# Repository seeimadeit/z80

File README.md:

# z80
my z80 based computer

my tools
---- arduino mega ----
during project startup im using it to provide a clock source and a serial port configured as a device on the z80 so I use it for basic keyboard IO.
the project will remove this at some point in the future..
https://www.arduino.cc/en/software

----- chip programmer ---
tl866II plus
www.xgecu.com
rom - at28c64b
gal - ATF16LV8CZ - provides logic for rom and ram selection.
source code for GAL and ROM available on github

------ svn tool ---
oxygenxml

----- gal programming language ----
wincupl

https://www.microchip.com/design-centers/fpgas-and-plds/splds-cplds/pld-design-resources

-------- rom code -----
vasm
http://sun.hasenbraten.de/vasm/
initial rom code written with vasm. I'll be moving to z88dk in the future.

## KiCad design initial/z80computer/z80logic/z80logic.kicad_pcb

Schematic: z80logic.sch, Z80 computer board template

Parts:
ANDWAIT1: SN74HC21N; DIP-14_W7.62mm_Socket
C1, C9: 0.1uF; C_Axial_L5.1mm_D3.1mm_P7.50mm_Horizontal
C2, C4, C12, C13: perf_9x4symbol; perf_9x4
C3: 1.0uF; C_Axial_L3.8mm_D2.6mm_P7.50mm_Horizontal
C5, C14, C15, C16, C17, C18, C19, C20: perf_13x4symbol; perf_13x4
C6, C10, C11: perf_12x4symbol; perf_12x4
C7, C8: perf_36x4symbol; perf_36x4
CLOCK1: PIC18F24Q10-xSP; DIP-28_W7.62mm
IOPORT1: GAL16V8; DIP-20_W7.62mm_Socket
J1: pin header 855-M20-9953645; PinHeader_2x36_P2.54mm_Horizontal
J2: Conn_02x03_Top_Bottom; PinHeader_2x03_P2.54mm_Horizontal
J3: Conn_02x03_Odd_Even; PinSocket_2x03_P2.54mm_Vertical
MEMCHIPSELECT1: MEMCHIPSELECT; DIP-20_W7.62mm_Socket
OR1: SN74LS32N; DIP-14_W7.62mm_Socket
R1, R2: 1K; R_Axial_DIN0207_L6.3mm_D2.5mm_P10.16mm_Horizontal
SW1: SW_SPST; SW_PUSH_6mm_H8mm

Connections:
/17: C7.33, C7.34, C7.35, C7.36, J1.17
/18: C8.33, C8.34, C8.35, C8.36, J1.18
/27: C7.53, C7.54, C7.55, C7.56, J1.27
/28: C8.53, C8.54, C8.55, C8.56, J1.28
/42: C8.81, C8.82, C8.83, C8.84, J1.42
/43: C7.85, C7.86, C7.87, C7.88, J1.43
/44: C8.85, C8.86, C8.87, C8.88, J1.44
/48: C8.93, C8.94, C8.95, C8.96, J1.48
/49: C7.97, C7.98, C7.99, C7.100, J1.49
/50: C8.97, C8.98, C8.99, C8.100, J1.50
/54: C8.105, C8.106, C8.107, C8.108, J1.54
/55: C7.109, C7.110, C7.111, C7.112, J1.55
/56: C8.109, C8.110, C8.111, C8.112, J1.56
/60: C8.117, C8.118, C8.119, C8.120, J1.60
/61: C7.121, C7.122, C7.123, C7.124, J1.61
/62: C8.121, C8.122, C8.123, C8.124, J1.62
/63: C7.125, C7.126, C7.127, C7.128, J1.63
/64: C8.125, C8.126, C8.127, C8.128, J1.64
/65: C7.129, C7.130, C7.131, C7.132, J1.65
/66: C8.129, C8.130, C8.131, C8.132, J1.66
/67: C7.133, C7.134, C7.135, C7.136, J1.67
/68: C8.133, C8.134, C8.135, C8.136, J1.68
/69: C7.137, C7.138, C7.139, C7.140, J1.69
/70: C8.137, C8.138, C8.139, C8.140, J1.70
/71: C7.141, C7.142, C7.143, C7.144, J1.71
/72: C8.141, C8.142, C8.143, C8.144, J1.72
/A0: C7.1, C7.2, C7.3, C7.4, C12.1, C12.2, C12.3, C12.4, IOPORT1.1, J1.1
/A1: C8.1, C8.2, C8.3, C8.4, C12.5, C12.6, C12.7, C12.8, IOPORT1.2, J1.2
/A1A: ANDWAIT1.1, C10.1, C10.2, C10.3, C10.4
/A1B: ANDWAIT1.2, C10.5, C10.6, C10.7, C10.8
/A1C: ANDWAIT1.4, C10.9, C10.10, C10.11, C10.12
/A1CS: C4.25, C4.26, C4.27, C4.28, C7.105, C7.106, C7.107, C7.108, J1.53, MEMCHIPSELECT1.13
/A1D: ANDWAIT1.5, C10.13, C10.14, C10.15, C10.16
/A1OE: C8.101, C8.102, C8.103, C8.104, J1.52
/A1WE: C7.101, C7.102, C7.103, C7.104, J1.51
/A1Y: ANDWAIT1.6, C10.17, C10.18, C10.19, C10.20
/A2: C7.5, C7.6, C7.7, C7.8, C12.9, C12.10, C12.11, C12.12, IOPORT1.3, J1.3
/A2A: ANDWAIT1.9, C10.21, C10.22, C10.23, C10.24
/A2B: ANDWAIT1.10, C10.25, C10.26, C10.27, C10.28
/A2C: ANDWAIT1.12, C10.29, C10.30, C10.31, C10.32
/A2CS: C4.21, C4.22, C4.23, C4.24, C7.117, C7.118, C7.119, C7.120, J1.59, MEMCHIPSELECT1.14
/A2D: ANDWAIT1.13, C10.33, C10.34, C10.35, C10.36
/A2OE: C8.113, C8.114, C8.115, C8.116, J1.58
/A2WE: C7.113, C7.114, C7.115, C7.116, J1.57
/A2Y: ANDWAIT1.8, C10.37, C10.38, C10.39, C10.40
/A3: C8.5, C8.6, C8.7, C8.8, C12.13, C12.14, C12.15, C12.16, IOPORT1.4, J1.4
/A4: C7.9, C7.10, C7.11, C7.12, J1.5
/A5: C8.9, C8.10, C8.11, C8.12, J1.6
/A6: C7.13, C7.14, C7.15, C7.16, J1.7
/A7: C8.13, C8.14, C8.15, C8.16, J1.8
/A8: C7.17, C7.18, C7.19, C7.20, J1.9
/A9: C8.17, C8.18, C8.19, C8.20, J1.10
/A10: C7.21, C7.22, C7.23, C7.24, J1.11
/A11: C2.17, C2.18, C2.19, C2.20, C8.21, C8.22, C8.23, C8.24, J1.12, MEMCHIPSELECT1.5
/A12: C2.21, C2.22, C2.23, C2.24, C7.25, C7.26, C7.27, C7.28, J1.13, MEMCHIPSELECT1.6
/A13: C2.25, C2.26, C2.27, C2.28, C8.25, C8.26, C8.27, C8.28, J1.14, MEMCHIPSELECT1.7
/A14: C2.29, C2.30, C2.31, C2.32, C7.29, C7.30, C7.31, C7.32, J1.15, MEMCHIPSELECT1.8
/A15: C2.33, C2.34, C2.35, C2.36, C8.29, C8.30, C8.31, C8.32, J1.16, MEMCHIPSELECT1.9
/BUSACK: C7.57, C7.58, C7.59, C7.60, J1.29
/BUSRQ: C8.57, C8.58, C8.59, C8.60, J1.30
/CLK: C5.33, C5.34, C5.35, C5.36, C7.81, C7.82, C7.83, C7.84, CLOCK1.10, J1.41
/D0: C7.37, C7.38, C7.39, C7.40, J1.19
/D1: C8.37, C8.38, C8.39, C8.40, J1.20
/D2: C7.41, C7.42, C7.43, C7.44, J1.21
/D3: C8.41, C8.42, C8.43, C8.44, J1.22
/D4: C7.45, C7.46, C7.47, C7.48, J1.23
/D5: C8.45, C8.46, C8.47, C8.48, J1.24
/D6: C7.49, C7.50, C7.51, C7.52, J1.25
/D7: C8.49, C8.50, C8.51, C8.52, J1.26
/GND: ANDWAIT1.7, C1.2, C3.2, C9.2, CLOCK1.19, IOPORT1.10, J2.6, J3.5, MEMCHIPSELECT1.10, OR1.7, SW1.2
/HALT: C7.69, C7.70, C7.71, C7.72, J1.35
/INT: C7.77, C7.78, C7.79, C7.80, J1.39
/IORQ: C4.9, C4.10, C4.11, C4.12, C7.61, C7.62, C7.63, C7.64, C12.17, C12.18, C12.19, C12.20, IOPORT1.5, J1.31, MEMCHIPSELECT1.17
/M1: C8.73, C8.74, C8.75, C8.76, C12.29, C12.30, C12.31, C12.32, IOPORT1.8, J1.38
/MREQ: C4.33, C4.34, C4.35, C4.36, C8.61, C8.62, C8.63, C8.64, J1.32, MEMCHIPSELECT1.11
/NMI: C8.77, C8.78, C8.79, C8.80, J1.40
/O1A: C11.1, C11.2, C11.3, C11.4, OR1.1
/O1B: C11.5, C11.6, C11.7, C11.8, OR1.2
/O1Y: C11.9, C11.10, C11.11, C11.12, OR1.3
/O2A: C11.13, C11.14, C11.15, C11.16, OR1.4
/O2B: C11.17, C11.18, C11.19, C11.20, OR1.5
/O2Y: C11.21, C11.22, C11.23, C11.24, OR1.6
/O3A: C11.25, C11.26, C11.27, C11.28, OR1.9
/O3B: C11.29, C11.30, C11.31, C11.32, OR1.10
/O3Y: C11.33, C11.34, C11.35, C11.36, OR1.8
/O4A: C11.37, C11.38, C11.39, C11.40, OR1.12
/O4B: C11.41, C11.42, C11.43, C11.44, OR1.13
/O4Y: C11.45, C11.46, C11.47, C11.48, OR1.11
/OCS: C4.29, C4.30, C4.31, C4.32, C7.93, C7.94, C7.95, C7.96, J1.47, MEMCHIPSELECT1.12
/OOE: C8.89, C8.90, C8.91, C8.92, J1.46
/OWE: C7.89, C7.90, C7.91, C7.92, J1.45
/POWER2: J2.2, J3.1
/POWER3: J2.3, J3.4
/PUSH: C6.41, C6.42, C6.43, C6.44, CLOCK1.16, R2.2
/RD: C8.65, C8.66, C8.67, C8.68, J1.34
/RESET: J2.1, J3.2
/RFSH: C4.17, C4.18, C4.19, C4.20, C7.73, C7.74, C7.75, C7.76, C12.21, C12.22, C12.23, C12.24, IOPORT1.6, J1.37, MEMCHIPSELECT1.15
/VCC3: J2.4, J3.3
/VCC5: ANDWAIT1.14, C1.1, C3.1, C5.1, C5.2, C5.3, C5.4, C9.1, C14.4, C14.8, C14.12, C14.16, C14.20, C14.24, C14.28, C14.32, C14.36, C14.40, C14.44, C14.48, C14.52, C17.49, C17.50, C17.51, C17.52, CLOCK1.1, CLOCK1.8, CLOCK1.20, IOPORT1.20, J2.5, J3.6, MEMCHIPSELECT1.20, OR1.14, R1.2
/WAIT: C8.69, C8.70, C8.71, C8.72, J1.36
/WR: C7.65, C7.66, C7.67, C7.68, J1.33
unnamed: C2.1, C2.2, C2.3, C2.4, MEMCHIPSELECT1.1
unnamed: C2.5, C2.6, C2.7, C2.8, MEMCHIPSELECT1.2
unnamed: C2.9, C2.10, C2.11, C2.12, MEMCHIPSELECT1.3
unnamed: C2.13, C2.14, C2.15, C2.16, MEMCHIPSELECT1.4
unnamed: C4.1, C4.2, C4.3, C4.4, MEMCHIPSELECT1.19
unnamed: C4.5, C4.6, C4.7, C4.8, MEMCHIPSELECT1.18
unnamed: C4.13, C4.14, C4.15, C4.16, MEMCHIPSELECT1.16
unnamed: C5.5, C5.6, C5.7, C5.8, CLOCK1.2
unnamed: C5.9, C5.10, C5.11, C5.12, CLOCK1.3
unnamed: C5.13, C5.14, C5.15, C5.16, CLOCK1.4
unnamed: C5.17, C5.18, C5.19, C5.20, CLOCK1.5
unnamed: C5.21, C5.22, C5.23, C5.24, CLOCK1.6
unnamed: C5.25, C5.26, C5.27, C5.28, CLOCK1.7
unnamed: C5.29, C5.30, C5.31, C5.32, CLOCK1.9
unnamed: C5.37, C5.38, C5.39, C5.40, CLOCK1.11
unnamed: C5.41, C5.42, C5.43, C5.44, CLOCK1.12
unnamed: C5.45, C5.46, C5.47, C5.48, CLOCK1.13
unnamed: C5.49, C5.50, C5.51, C5.52, CLOCK1.14
unnamed: C6.1, C6.2, C6.3, C6.4, CLOCK1.28
unnamed: C6.5, C6.6, C6.7, C6.8, CLOCK1.27
unnamed: C6.9, C6.10, C6.11, C6.12, CLOCK1.26
unnamed: C6.13, C6.14, C6.15, C6.16, CLOCK1.25
unnamed: C6.17, C6.18, C6.19, C6.20, CLOCK1.24
unnamed: C6.21, C6.22, C6.23, C6.24, CLOCK1.23
unnamed: C6.25, C6.26, C6.27, C6.28, CLOCK1.22
unnamed: C6.29, C6.30, C6.31, C6.32, CLOCK1.21
unnamed: C6.33, C6.34, C6.35, C6.36, CLOCK1.18
unnamed: C6.37, C6.38, C6.39, C6.40, CLOCK1.17
unnamed: C6.45, C6.46, C6.47, C6.48, CLOCK1.15
unnamed: C10.41, C10.42, C10.43, C10.44
unnamed: C10.45, C10.46, C10.47, C10.48
unnamed: C12.25, C12.26, C12.27, C12.28, IOPORT1.7
unnamed: C12.33, C12.34, C12.35, C12.36, IOPORT1.9
unnamed: C13.1, C13.2, C13.3, C13.4, IOPORT1.19
unnamed: C13.5, C13.6, C13.7, C13.8, IOPORT1.18
unnamed: C13.9, C13.10, C13.11, C13.12, IOPORT1.17
unnamed: C13.13, C13.14, C13.15, C13.16, IOPORT1.16
unnamed: C13.17, C13.18, C13.19, C13.20, IOPORT1.15
unnamed: C13.21, C13.22, C13.23, C13.24, IOPORT1.14
unnamed: C13.25, C13.26, C13.27, C13.28, IOPORT1.13
unnamed: C13.29, C13.30, C13.31, C13.32, IOPORT1.12
unnamed: C13.33, C13.34, C13.35, C13.36, IOPORT1.11
unnamed: R1.1, R2.1, SW1.1

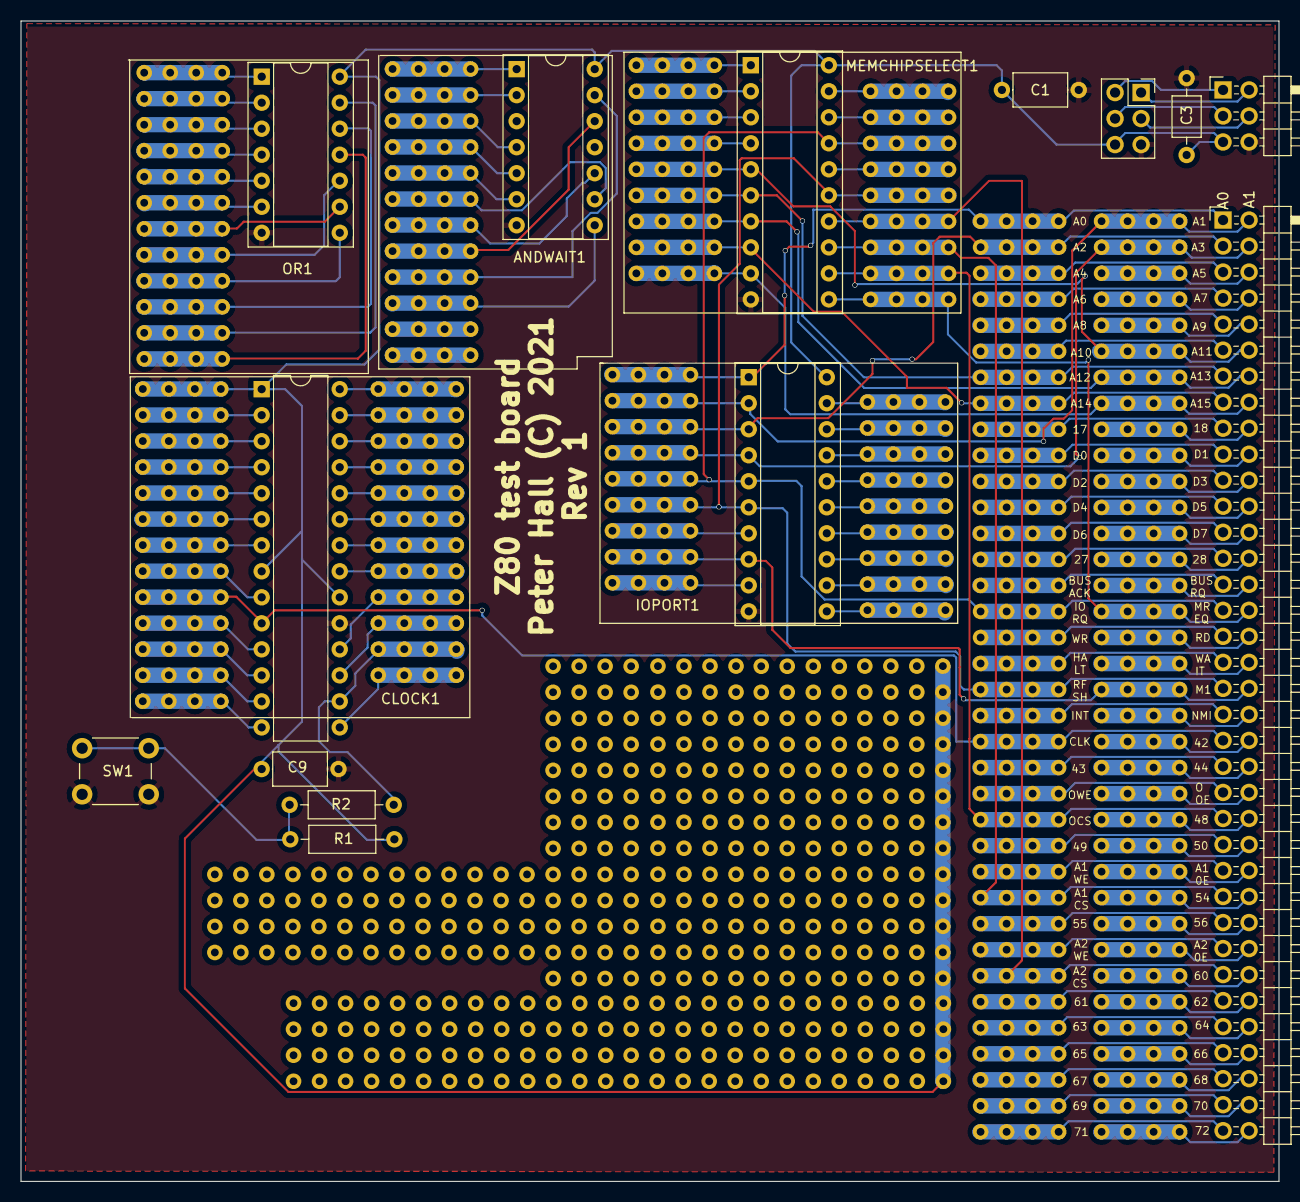
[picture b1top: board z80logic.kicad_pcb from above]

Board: 2 copper layers, 122.8 x 113.3 mm, 31 parts (0 on the bottom side), 144 nets.

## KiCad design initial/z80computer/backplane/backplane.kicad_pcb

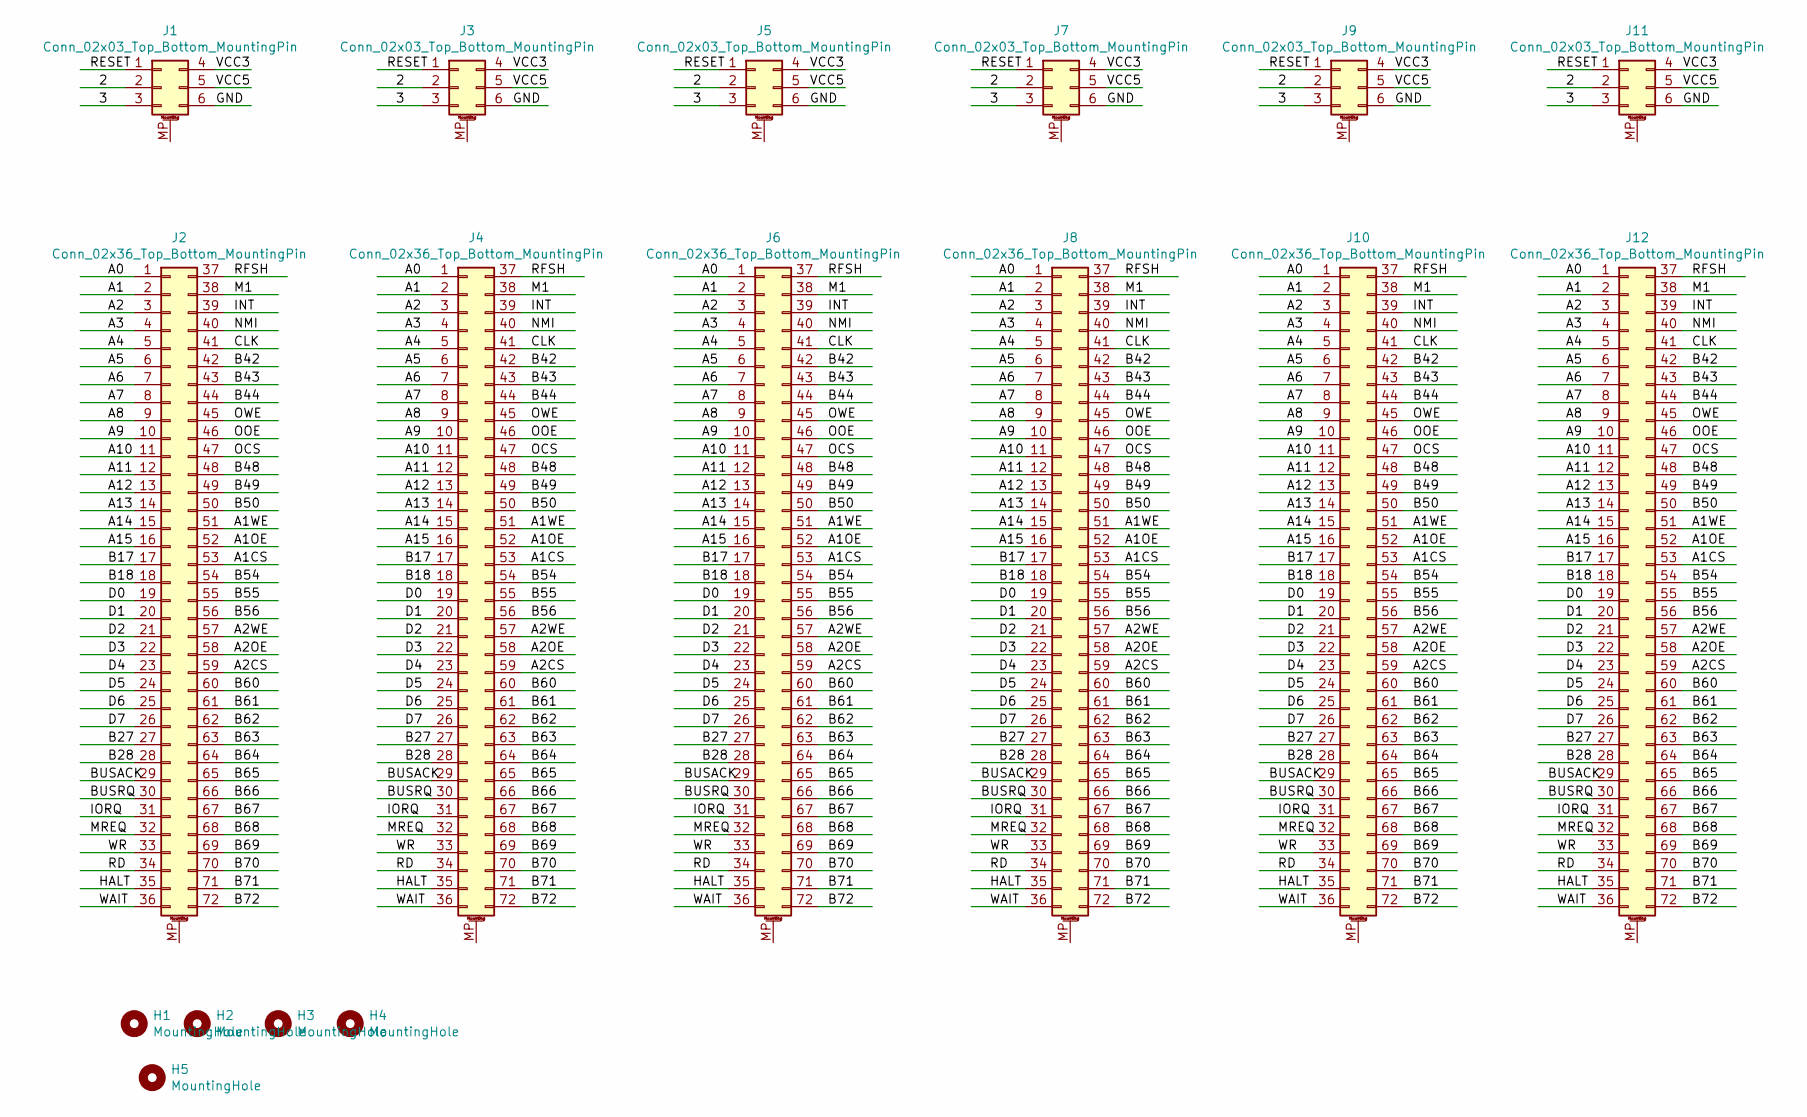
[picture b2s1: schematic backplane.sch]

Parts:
H1, H2, H3, H4: MountingHole; MountingHole_3mm_Pad_TopBottom
H5: MountingHole; MountingHole_2.1mm
J1, J3, J5, J7, J9, J11: Conn_02x03_Top_Bottom_MountingPin; PinSocket_2x03_P2.54mm_Vertical
J2, J4, J6, J8, J10, J12: Conn_02x36_Top_Bottom_MountingPin; PinSocket_2x36_P2.54mm_Vertical

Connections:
/2: J1.2, J3.2, J5.2, J7.2, J9.2, J11.2
/3: J1.3, J3.3, J5.3, J7.3, J9.3, J11.3
/A0: J2.1, J4.1, J6.1, J8.1, J10.1, J12.1
/A1: J2.2, J4.2, J6.2, J8.2, J10.2, J12.2
/A1CS: J2.53, J4.53, J6.53, J8.53, J10.53, J12.53
/A1OE: J2.52, J4.52, J6.52, J8.52, J10.52, J12.52
/A1WE: J2.51, J4.51, J6.51, J8.51, J10.51, J12.51
/A2: J2.3, J4.3, J6.3, J8.3, J10.3, J12.3
/A2CS: J2.59, J4.59, J6.59, J8.59, J10.59, J12.59
/A2OE: J2.58, J4.58, J6.58, J8.58, J10.58, J12.58
/A2WE: J2.57, J4.57, J6.57, J8.57, J10.57, J12.57
/A3: J2.4, J4.4, J6.4, J8.4, J10.4, J12.4
/A4: J2.5, J4.5, J6.5, J8.5, J10.5, J12.5
/A5: J2.6, J4.6, J6.6, J8.6, J10.6, J12.6
/A6: J2.7, J4.7, J6.7, J8.7, J10.7, J12.7
/A7: J2.8, J4.8, J6.8, J8.8, J10.8, J12.8
/A8: J2.9, J4.9, J6.9, J8.9, J10.9, J12.9
/A9: J2.10, J4.10, J6.10, J8.10, J10.10, J12.10
/A10: J2.11, J4.11, J6.11, J8.11, J10.11, J12.11
/A11: J2.12, J4.12, J6.12, J8.12, J10.12, J12.12
/A12: J2.13, J4.13, J6.13, J8.13, J10.13, J12.13
/A13: J2.14, J4.14, J6.14, J8.14, J10.14, J12.14
/A14: J2.15, J4.15, J6.15, J8.15, J10.15, J12.15
/A15: J2.16, J4.16, J6.16, J8.16, J10.16, J12.16
/B17: J2.17, J4.17, J6.17, J8.17, J10.17, J12.17
/B18: J2.18, J4.18, J6.18, J8.18, J10.18, J12.18
/B27: J2.27, J4.27, J6.27, J8.27, J10.27, J12.27
/B28: J2.28, J4.28, J6.28, J8.28, J10.28, J12.28
/B42: J2.42, J4.42, J6.42, J8.42, J10.42, J12.42
/B43: J2.43, J4.43, J6.43, J8.43, J10.43, J12.43
/B44: J2.44, J4.44, J6.44, J8.44, J10.44, J12.44
/B48: J2.48, J4.48, J6.48, J8.48, J10.48, J12.48
/B49: J2.49, J4.49, J6.49, J8.49, J10.49, J12.49
/B50: J2.50, J4.50, J6.50, J8.50, J10.50, J12.50
/B54: J2.54, J4.54, J6.54, J8.54, J10.54, J12.54
/B55: J2.55, J4.55, J6.55, J8.55, J10.55, J12.55
/B56: J2.56, J4.56, J6.56, J8.56, J10.56, J12.56
/B60: J2.60, J4.60, J6.60, J8.60, J10.60, J12.60
/B61: J2.61, J4.61, J6.61, J8.61, J10.61, J12.61
/B62: J2.62, J4.62, J6.62, J8.62, J10.62, J12.62
/B63: J2.63, J4.63, J6.63, J8.63, J10.63, J12.63
/B64: J2.64, J4.64, J6.64, J8.64, J10.64, J12.64
/B65: J2.65, J4.65, J6.65, J8.65, J10.65, J12.65
/B66: J2.66, J4.66, J6.66, J8.66, J10.66, J12.66
/B67: J2.67, J4.67, J6.67, J8.67, J10.67, J12.67
/B68: J2.68, J4.68, J6.68, J8.68, J10.68, J12.68
/B69: J2.69, J4.69, J6.69, J8.69, J10.69, J12.69
/B70: J2.70, J4.70, J6.70, J8.70, J10.70, J12.70
/B71: J2.71, J4.71, J6.71, J8.71, J10.71, J12.71
/B72: J2.72, J4.72, J6.72, J8.72, J10.72, J12.72
/BUSACK: J2.29, J4.29, J6.29, J8.29, J10.29, J12.29
/BUSRQ: J2.30, J4.30, J6.30, J8.30, J10.30, J12.30
/CLK: J2.41, J4.41, J6.41, J8.41, J10.41, J12.41
/D0: J2.19, J4.19, J6.19, J8.19, J10.19, J12.19
/D1: J2.20, J4.20, J6.20, J8.20, J10.20, J12.20
/D2: J2.21, J4.21, J6.21, J8.21, J10.21, J12.21
/D3: J2.22, J4.22, J6.22, J8.22, J10.22, J12.22
/D4: J2.23, J4.23, J6.23, J8.23, J10.23, J12.23
/D5: J2.24, J4.24, J6.24, J8.24, J10.24, J12.24
/D6: J2.25, J4.25, J6.25, J8.25, J10.25, J12.25
/D7: J2.26, J4.26, J6.26, J8.26, J10.26, J12.26
/GND: J1.6, J3.6, J5.6, J7.6, J9.6, J11.6
/HALT: J2.35, J4.35, J6.35, J8.35, J10.35, J12.35
/INT: J2.39, J4.39, J6.39, J8.39, J10.39, J12.39
/IORQ: J2.31, J4.31, J6.31, J8.31, J10.31, J12.31
/M1: J2.38, J4.38, J6.38, J8.38, J10.38, J12.38
/MREQ: J2.32, J4.32, J6.32, J8.32, J10.32, J12.32
/NMI: J2.40, J4.40, J6.40, J8.40, J10.40, J12.40
/OCS: J2.47, J4.47, J6.47, J8.47, J10.47, J12.47
/OOE: J2.46, J4.46, J6.46, J8.46, J10.46, J12.46
/OWE: J2.45, J4.45, J6.45, J8.45, J10.45, J12.45
/RD: J2.34, J4.34, J6.34, J8.34, J10.34, J12.34
/RESET: J1.1, J3.1, J5.1, J7.1, J9.1, J11.1
/RFSH: J2.37, J4.37, J6.37, J8.37, J10.37, J12.37
/VCC3: J1.4, J3.4, J5.4, J7.4, J9.4, J11.4
/VCC5: J1.5, J3.5, J5.5, J7.5, J9.5, J11.5
/WAIT: J2.36, J4.36, J6.36, J8.36, J10.36, J12.36
/WR: J2.33, J4.33, J6.33, J8.33, J10.33, J12.33

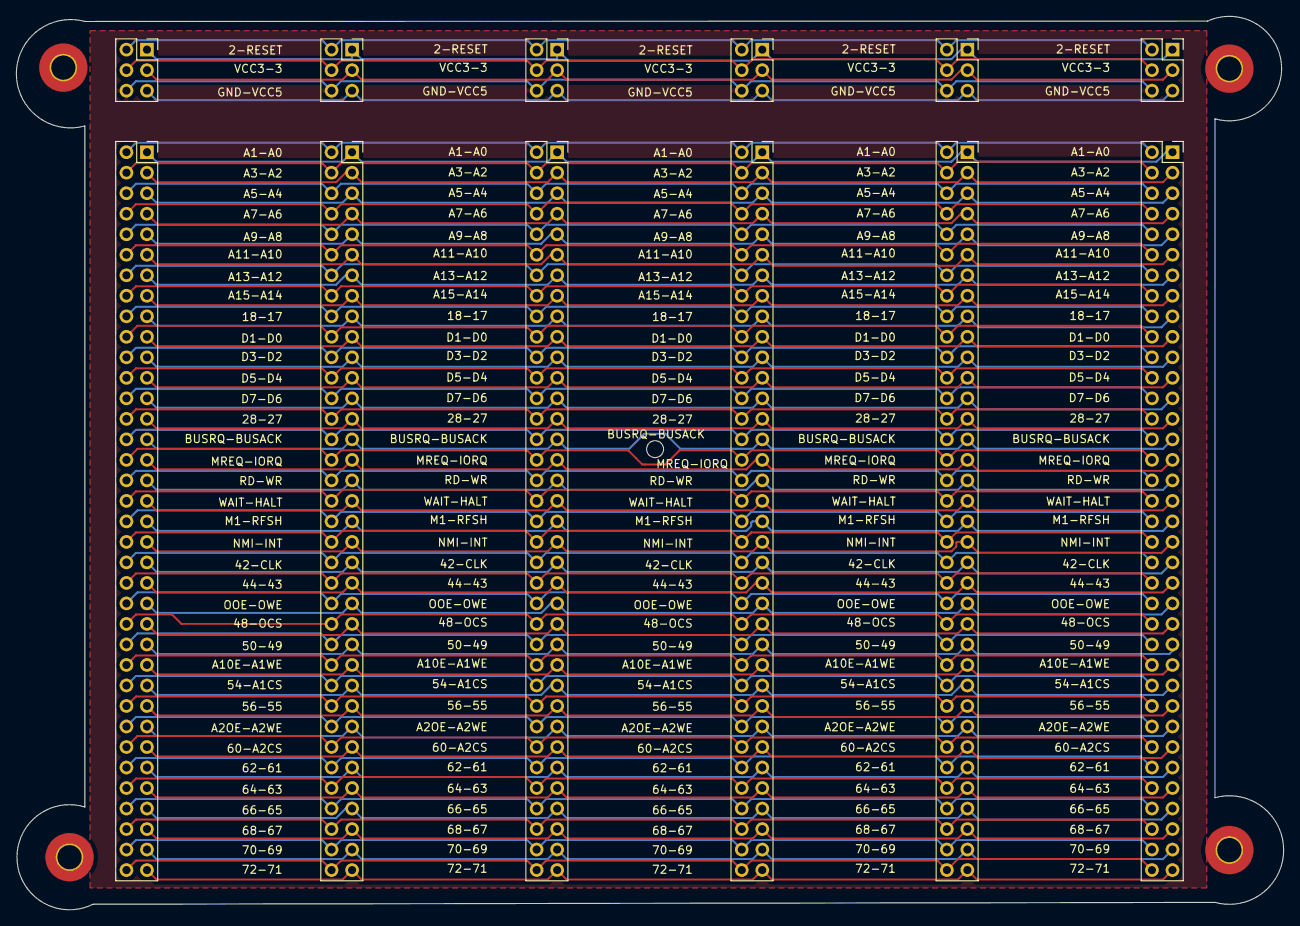
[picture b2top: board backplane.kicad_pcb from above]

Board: 2 copper layers, 156.9 x 110.6 mm, 17 parts (0 on the bottom side), 78 nets.

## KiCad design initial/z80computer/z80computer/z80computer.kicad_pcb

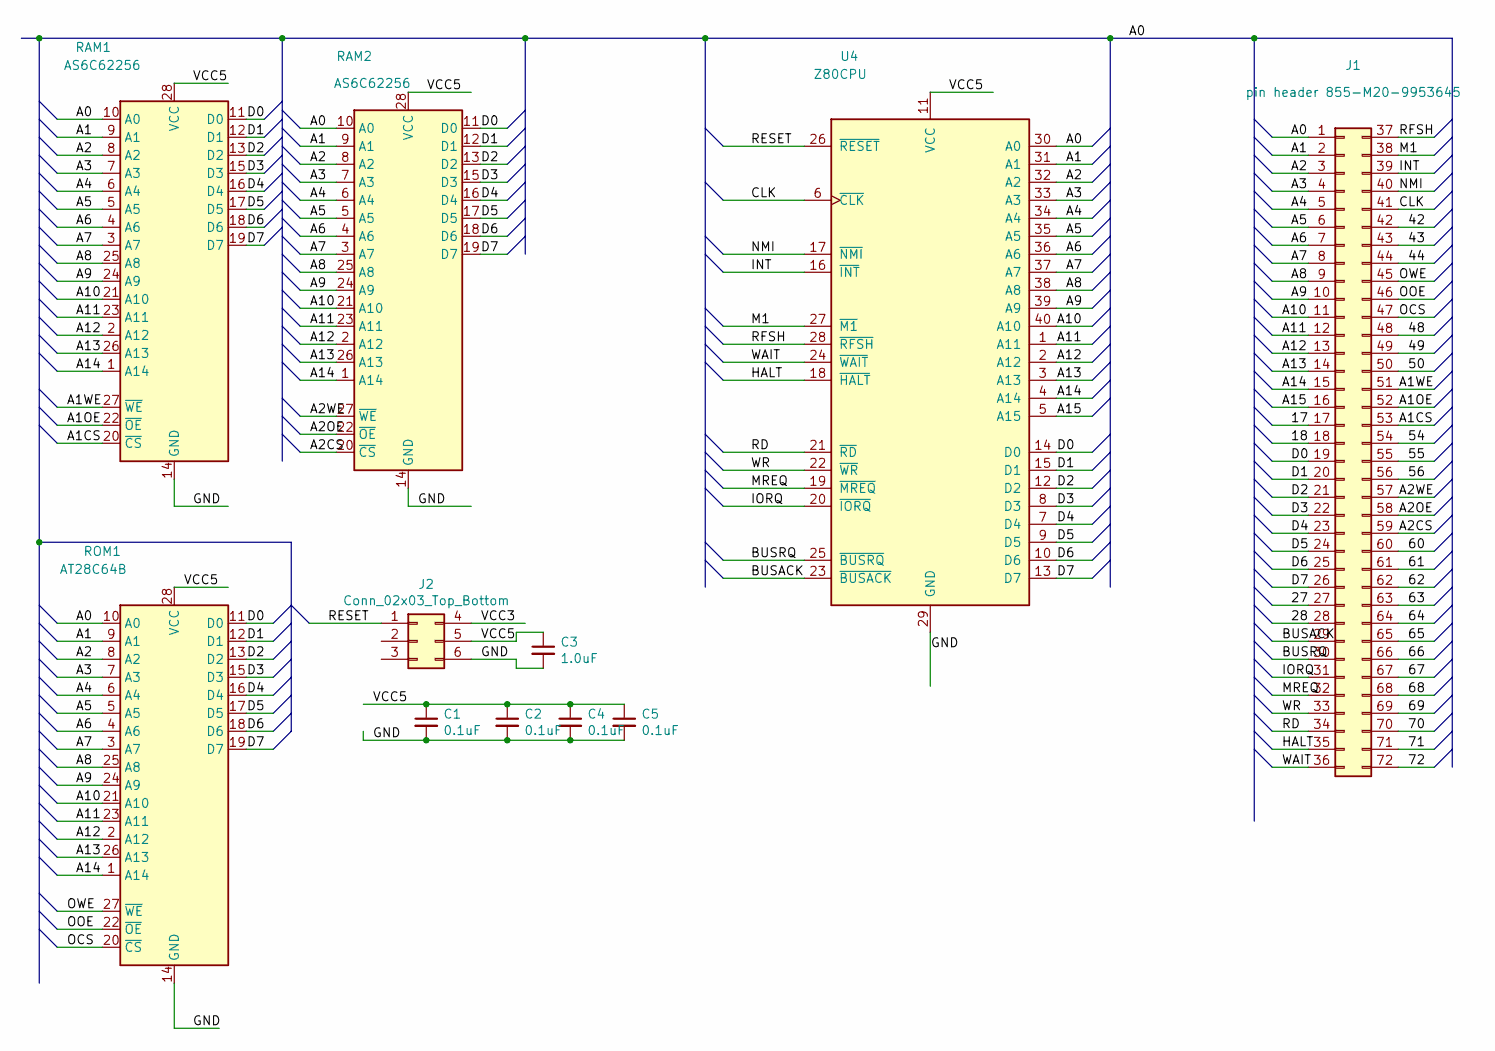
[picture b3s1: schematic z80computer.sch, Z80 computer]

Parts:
C1, C2, C4, C5: 0.1uF; C_Axial_L5.1mm_D3.1mm_P7.50mm_Horizontal
C3: 1.0uF; C_Axial_L3.8mm_D2.6mm_P7.50mm_Horizontal
J1: pin header 855-M20-9953645; PinHeader_2x36_P2.54mm_Horizontal
J2: Conn_02x03_Top_Bottom; PinHeader_2x03_P2.54mm_Horizontal
RAM1, RAM2: AS6C62256; DIP-28_W15.24mm_Socket_LongPads
ROM1: AT28C64B; DIP-28_W15.24mm_Socket_LongPads
U4: Z80CPU; DIP-40_W15.24mm_Socket_LongPads

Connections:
/A0: J1.1, RAM1.10 (A0), RAM2.10 (A0), ROM1.10 (A0), U4.30 (A0)
/A1: J1.2, RAM1.9 (A1), RAM2.9 (A1), ROM1.9 (A1), U4.31 (A1)
/A1CS: J1.53, RAM1.20 (~CS)
/A1OE: J1.52, RAM1.22 (~OE)
/A1WE: J1.51, RAM1.27 (~WE)
/A2: J1.3, RAM1.8 (A2), RAM2.8 (A2), ROM1.8 (A2), U4.32 (A2)
/A2CS: J1.59, RAM2.20 (~CS)
/A2OE: J1.58, RAM2.22 (~OE)
/A2WE: J1.57, RAM2.27 (~WE)
/A3: J1.4, RAM1.7 (A3), RAM2.7 (A3), ROM1.7 (A3), U4.33 (A3)
/A4: J1.5, RAM1.6 (A4), RAM2.6 (A4), ROM1.6 (A4), U4.34 (A4)
/A5: J1.6, RAM1.5 (A5), RAM2.5 (A5), ROM1.5 (A5), U4.35 (A5)
/A6: J1.7, RAM1.4 (A6), RAM2.4 (A6), ROM1.4 (A6), U4.36 (A6)
/A7: J1.8, RAM1.3 (A7), RAM2.3 (A7), ROM1.3 (A7), U4.37 (A7)
/A8: J1.9, RAM1.25 (A8), RAM2.25 (A8), ROM1.25 (A8), U4.38 (A8)
/A9: J1.10, RAM1.24 (A9), RAM2.24 (A9), ROM1.24 (A9), U4.39 (A9)
/A10: J1.11, RAM1.21 (A10), RAM2.21 (A10), ROM1.21 (A10), U4.40 (A10)
/A11: J1.12, RAM1.23 (A11), RAM2.23 (A11), ROM1.23 (A11), U4.1 (A11)
/A12: J1.13, RAM1.2 (A12), RAM2.2 (A12), ROM1.2 (A12), U4.2 (A12)
/A13: J1.14, RAM1.26 (A13), RAM2.26 (A13), ROM1.26 (A13), U4.3 (A13)
/A14: J1.15, RAM1.1 (A14), RAM2.1 (A14), ROM1.1 (A14), U4.4 (A14)
/A15: J1.16, U4.5 (A15)
/BUSACK: J1.29, U4.23 (~BUSACK~)
/BUSRQ: J1.30, U4.25 (~BUSRQ~)
/CLK: J1.41, U4.6 (~CLK~)
/D0: J1.19, RAM1.11 (D0), RAM2.11 (D0), ROM1.11 (D0), U4.14 (D0)
/D1: J1.20, RAM1.12 (D1), RAM2.12 (D1), ROM1.12 (D1), U4.15 (D1)
/D2: J1.21, RAM1.13 (D2), RAM2.13 (D2), ROM1.13 (D2), U4.12 (D2)
/D3: J1.22, RAM1.15 (D3), RAM2.15 (D3), ROM1.15 (D3), U4.8 (D3)
/D4: J1.23, RAM1.16 (D4), RAM2.16 (D4), ROM1.16 (D4), U4.7 (D4)
/D5: J1.24, RAM1.17 (D5), RAM2.17 (D5), ROM1.17 (D5), U4.9 (D5)
/D6: J1.25, RAM1.18 (D6), RAM2.18 (D6), ROM1.18 (D6), U4.10 (D6)
/D7: J1.26, RAM1.19 (D7), RAM2.19 (D7), ROM1.19 (D7), U4.13 (D7)
/GND: C1.2, C2.2, C3.2, C4.2, C5.2, J2.6, RAM1.14 (GND), RAM2.14 (GND), ROM1.14 (GND), U4.29 (GND)
/HALT: J1.35, U4.18 (~HALT~)
/INT: J1.39, U4.16 (~INT~)
/IORQ: J1.31, U4.20 (~IORQ~)
/M1: J1.38, U4.27 (~M1~)
/MREQ: J1.32, U4.19 (~MREQ~)
/NMI: J1.40, U4.17 (~NMI~)
/OCS: J1.47, ROM1.20 (~CS)
/OOE: J1.46, ROM1.22 (~OE)
/OWE: J1.45, ROM1.27 (~WE)
/RD: J1.34, U4.21 (~RD~)
/RESET: J2.1, U4.26 (~RESET~)
/RFSH: J1.37, U4.28 (~RFSH~)
/VCC3: J2.4
/VCC5: C1.1, C2.1, C3.1, C4.1, C5.1, J2.5, RAM1.28 (VCC), RAM2.28 (VCC), ROM1.28 (VCC), U4.11 (VCC)
/WAIT: J1.36, U4.24 (~WAIT~)
/WR: J1.33, U4.22 (~WR~)

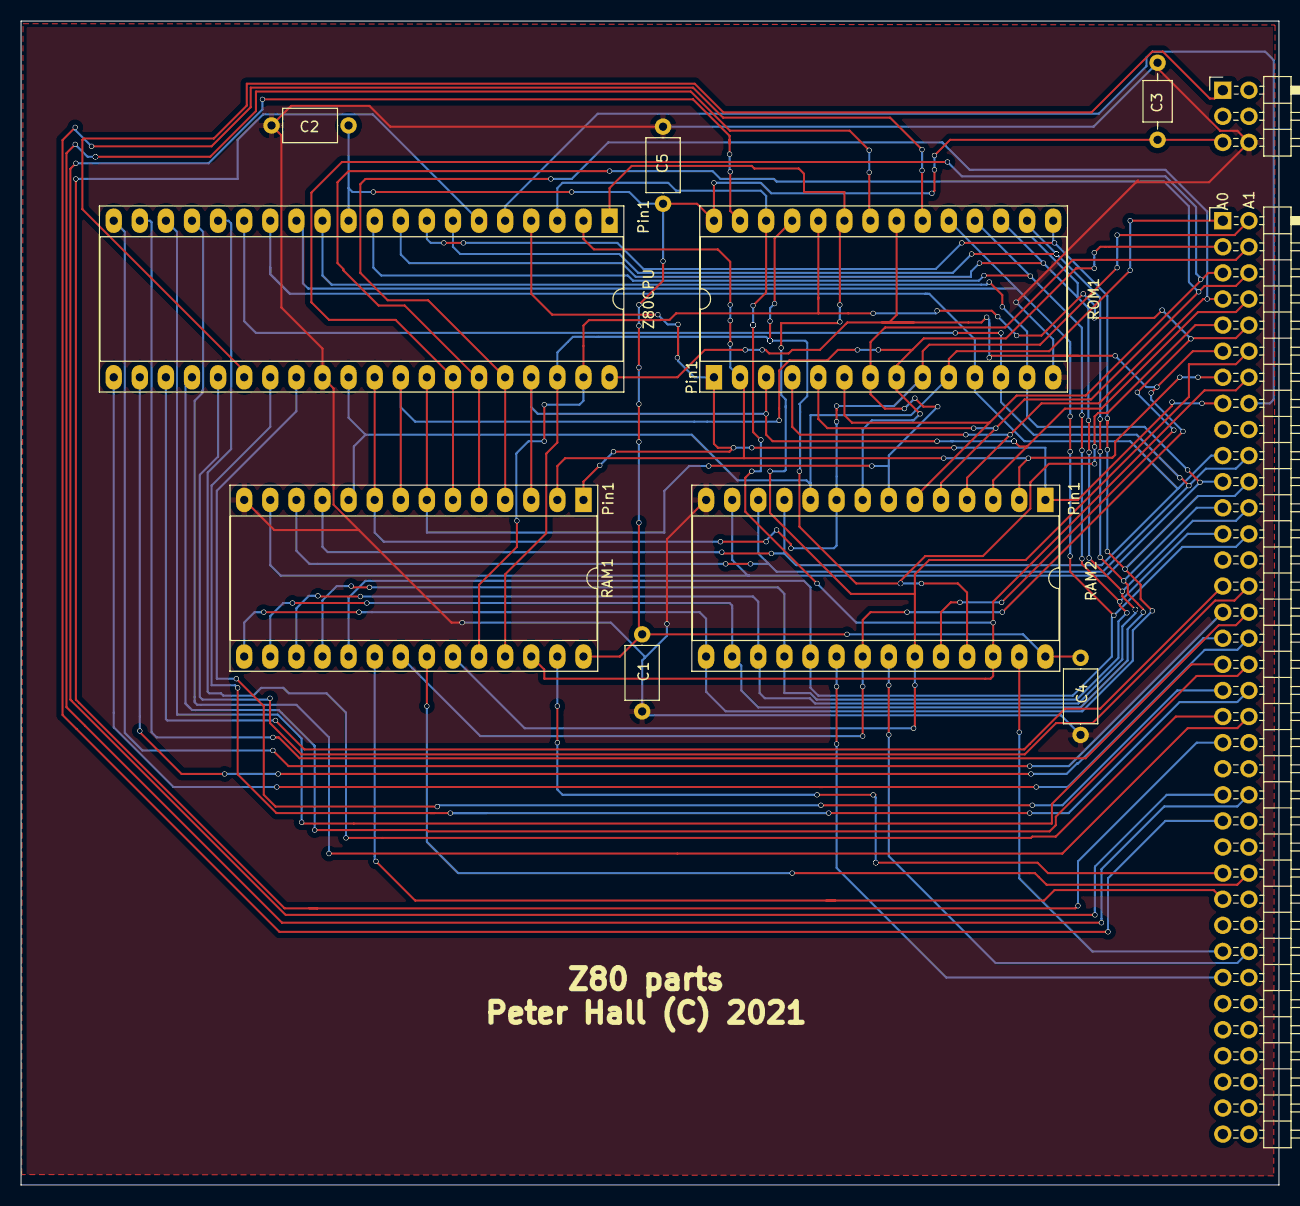
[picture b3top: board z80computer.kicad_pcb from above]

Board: 2 copper layers, 122.4 x 113.3 mm, 11 parts (0 on the bottom side), 49 nets.

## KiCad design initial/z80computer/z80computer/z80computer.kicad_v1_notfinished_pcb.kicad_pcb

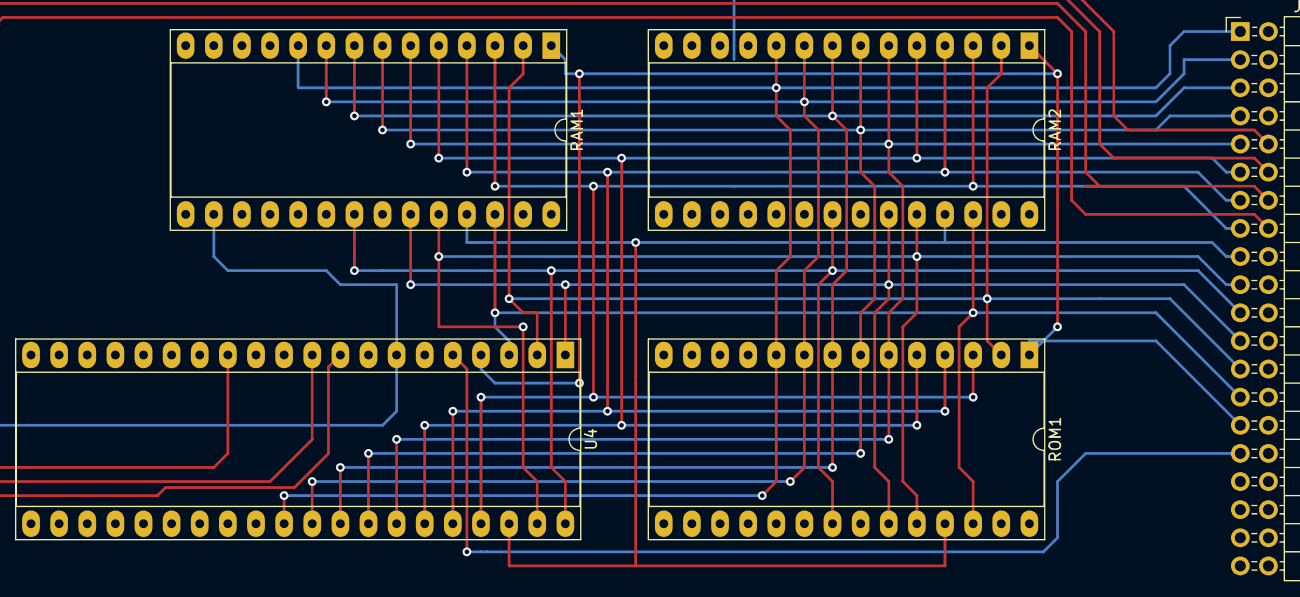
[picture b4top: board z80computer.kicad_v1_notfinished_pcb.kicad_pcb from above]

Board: 2 copper layers, 5 parts (0 on the bottom side), 24 nets.

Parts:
J1: Conn_02x20_Top_Bottom; PinHeader_2x20_P2.54mm_Horizontal
RAM1, RAM2: AS6C62256; DIP-28_W15.24mm_Socket_LongPads
ROM1: AT28C64B; DIP-28_W15.24mm_Socket_LongPads
U4: Z80CPU; DIP-40_W15.24mm_Socket_LongPads

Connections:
/A0: J1.1, RAM1.10, RAM2.10, ROM1.10, U4.30
/A1: J1.3, RAM1.9, RAM2.9, ROM1.9, U4.31
/A2: J1.5, RAM1.8, RAM2.8, ROM1.8, U4.32
/A3: J1.7, RAM1.7, RAM2.7, ROM1.7, U4.33
/A4: J1.9, RAM1.6, RAM2.6, ROM1.6, U4.34
/A5: J1.11, RAM1.5, RAM2.5, ROM1.5, U4.35
/A6: J1.13, RAM1.4, RAM2.4, ROM1.4, U4.36
/A7: J1.15, RAM1.3, RAM2.3, ROM1.3, U4.37
/A8: J1.17, RAM1.25, RAM2.25, ROM1.25, U4.38
/A9: J1.19, RAM1.24, RAM2.24, ROM1.24, U4.39
/A10: J1.21, RAM1.21, RAM2.21, ROM1.21, U4.40
/A11: J1.23, RAM1.23, RAM2.23, ROM1.23, U4.1
/A12: J1.25, RAM1.2, RAM2.2, ROM1.2, U4.2
/A13: J1.27, RAM1.26, RAM2.26, ROM1.26, U4.3
/A14: J1.29, RAM1.1, RAM2.1, ROM1.1, U4.4
/A15: J1.31, U4.5
/D0: J1.2, RAM1.11, RAM2.11, ROM1.11, U4.14
/D1: J1.4, RAM1.12, RAM2.12, ROM1.12, U4.15
/D2: J1.6, RAM1.13, RAM2.13, ROM1.13, U4.12
/D3: J1.8, RAM1.15, RAM2.15, ROM1.15, U4.8
/D4: J1.10, RAM1.16, RAM2.16, ROM1.16, U4.7
/D5: J1.12, RAM1.17, RAM2.17, ROM1.17, U4.9
/D6: J1.14, RAM1.18, RAM2.18, ROM1.18, U4.10
/D7: J1.16, RAM1.19, RAM2.19, ROM1.19, U4.13

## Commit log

2020-11-12 initial project files.
2020-11-15 current state: serial port to/from putty is working. reading the sd card and echoing the data to the serial port is working keypress interrupts are not currently working. no idea why.
2020-11-17 available returns true or value.
2020-11-20 added serial port pins now 19 sdcard = io port 0101 20 serial = io port 0001
2020-11-24 add refresh pin - because it was causing chipselects to happen during a refresh. it appeared to randomly write into the rom and corrupt it.
2020-11-24 changed board layout to use logic chip to select active device for IO port operations. this removed 8 pins from the requirements and added 1 new pin. code restructured to use interrupt mode 1
2020-11-24 changed board layout to use logic chip to select active device for IO port operations. this removed 8 pins from the requirements and added 1 new pin. code restructured to use interrupt mode 1 removed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
2020-11-24 code fixed to work in mode1 or mode 2. note: the sequence of instructions is vital. to use mode 2, the im 2 instruction must be executed but loading the I register. im 2 #; is vital that the sequece 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
2020-11-25 I increased the clock pulse. I tested the circuit with a 1mhz clock. the computer fails to run correctly. I attribute this to the slow processing of the arduinos. i've ordered some pic18 uC's that ru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
2020-11-25 a small boot rom. does nothing more than load the RAM image from SD card and runs it
2020-11-25 minimal OS RAM image. this is the basis of the OS. it does nothing except echo the characters from the keyboard. keyboard runs in mode 2
2020-11-26 command line prompt is now minimal but working. added a new command 'hello' which will print a hello world message. currently programs are stored on the SD card.
2020-11-26 just making a save
2020-11-27 just a backup
2020-11-27 hexdump and load now working in the command processor
2020-11-27 fixed stuff
2020-11-28 added functionally to open for writing, getfilename, get directory listing. write to file
2020-11-28 extended commandline add some new commands
2020-11-29 made several changes. the hexdump program is unfinished. I did get to add a createprocess function in the kernal. it's primative but making good progress
2020-11-30 sd card is initalized if the file open failed. this is required because each time the card is removed it wouldn't read it again until it was initialized. during an open is the best time to test for t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
2020-11-30 add highlight to cmd/hexdump. will also display hex from page boundary
2020-12-01 added much needed delete/backspace - horray
2020-12-11 just a quick save of everything
2020-12-11 added adjustable cpu clock for development purposes
2020-12-11 removed clock code from arduino controller_logicboardv4 fixed a startup frequency on pic clock
2020-12-19 the wait logic for serialport1 has changed. this chip will now set the wait condition. the uController is responsible to reset the wait condition. I did this because the logic chip can react faster t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
2020-12-19 changed the default clock speed to 31khz - oooo so fast
2020-12-19 changed the wait logic, this ucontroller only resets the wait flag on the logic chip (SDCARD), removed the clock reminants
2020-12-19 I don't remember
2020-12-21 some performance improvements
2020-12-24 playing around
2020-12-25 rename and organized stuff
2020-12-25 previous comment was wrong, it should say, the createprocess function now loads programs and libraries to the address specified in the file it's loading. ie. it no longer hardcoded. allowing multiple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
2020-12-26 change kernel to load cmd from address defined in cmd. added program header information. now contains loadaddress 2bytes memory required in pages 1byte stack required in pages 1byte
2020-12-26 testing markdown
2020-12-26 adding documentation
2020-12-26 added buildin command 'm*' to display the memory map table from cmd. malloctable is stored and managed in the kernel (it will be some day)
2020-12-27 documentation update
2020-12-27 kernel is recording malloctable entries during executable loads. there is no way to remove the entries at present
2020-12-28 fixed userMemory-50 reference with a real memory variable location
2020-12-29 fixed some bugs, add non working processinfo
2020-12-29 when a process is created it now updates the processinfo table. it doesn't remove the entries yet.
2020-12-29 added program entry address to the processinfo.
2021-01-01 added processor design board
2021-01-03 added kicad template for board designs. also has currentv version of the boards ( back plane and processor board)
2021-01-08 version 1 circuit boards

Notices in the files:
initial/z80computer/backplane/backplane.kicad_pcb:
Peter Hall (C) 2021
